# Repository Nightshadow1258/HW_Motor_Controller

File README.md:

# Motor Controller Board - Hardware
Hardware design files and documentation for the 3-phase custom Motor Controller Board (Hardware Revision v1.0). This board is designed for precise BLDC motor control, featuring integrated current sensing, reverse polarity protection, dynamic gate driving, and onboard networking interfaces.
## Board Status
- Current Hardware Version: v1.0
- Status: Tested & Verified (Timer PWM generation, ADC sampling, and hardware bringup verified)
## Key Hardware Components
- MCU: STM32H750VB — High-performance ARM Cortex-M7 Microcontroller (16-bit ADCs, TIM1 Advanced Timer)
- Gate Driver Unit (GDU): DRV8334 — 3-Phase Smart Gate Driver with integrated Current Sense Amplifiers (CSA)
- Ethernet PHY: LAN8742A — 10/100 Ethernet Transceiver for high-speed network communication
- CAN Transceiver: TJA1043T — High-speed CAN Transceiver with sleep mode and wake-up capabilities
- Reverse Polarity Protection (RPP): LM74700 — Ideal Diode Controller for low-loss battery/power reverse polarity protection
- Thermal Sensor: NTCS0603E3103FLT — 10kΩ NTC Thermistor for board temperature monitoring
## Repository Contents
- `/KiCAD` - source schematics files
- `/Documentation/Schematics` — schematic PDF export

# Related Resources
- Firmware Repository: [Motor Controller Board Firmware](https://github.com/Nightshadow1258/FW_STM32H750VB_DRV8334)
- Blog Posts:
	- [Part I - Hardware Design & Bringup](https://blog.preisch.cloud/diy-motor-controller-part-i-hardware-design-bringup/)

# License
This hardware design is licensed under the CERN-OHL-P v2

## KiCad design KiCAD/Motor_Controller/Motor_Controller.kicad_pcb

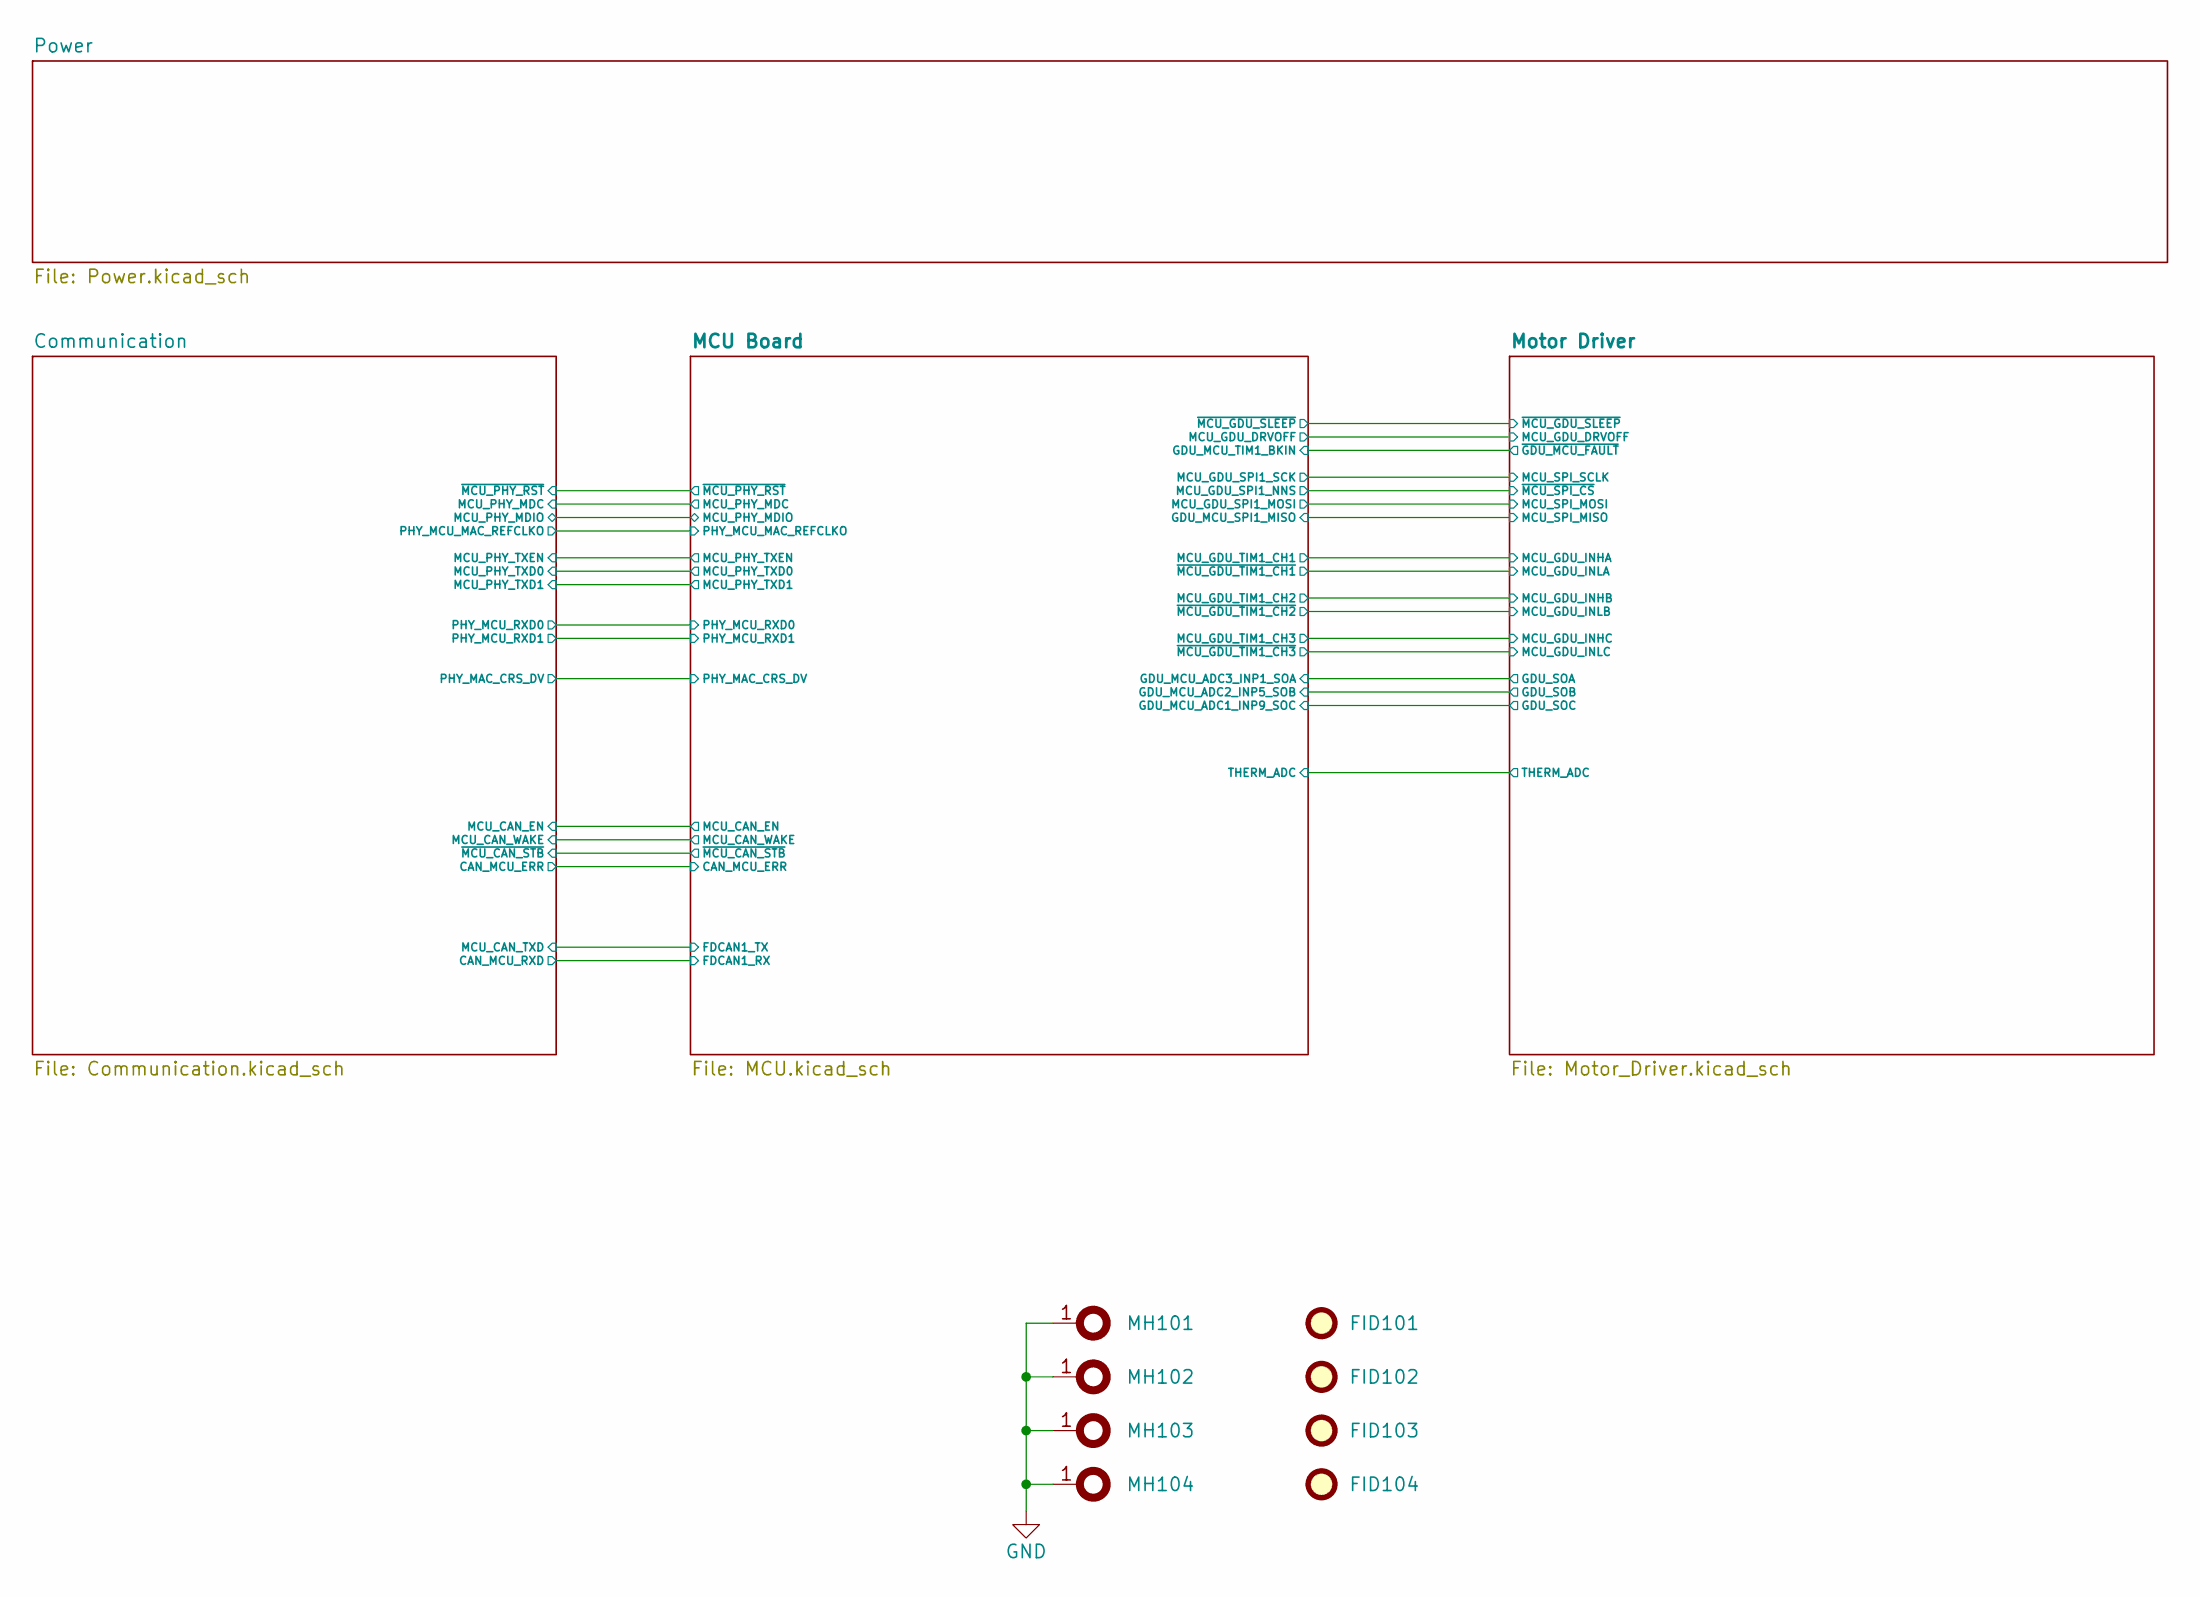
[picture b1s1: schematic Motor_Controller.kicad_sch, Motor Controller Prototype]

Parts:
FID101, FID102, FID103, FID104: Fiducal-JLCPPCB; PCB-FID-JLCPCB
MH101, MH102, MH103, MH104: MountingHole_3.2mm_M3_Pad_Via

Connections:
GND: MH101.1, MH102.1, MH103.1, MH104.1; also elsewhere on the board

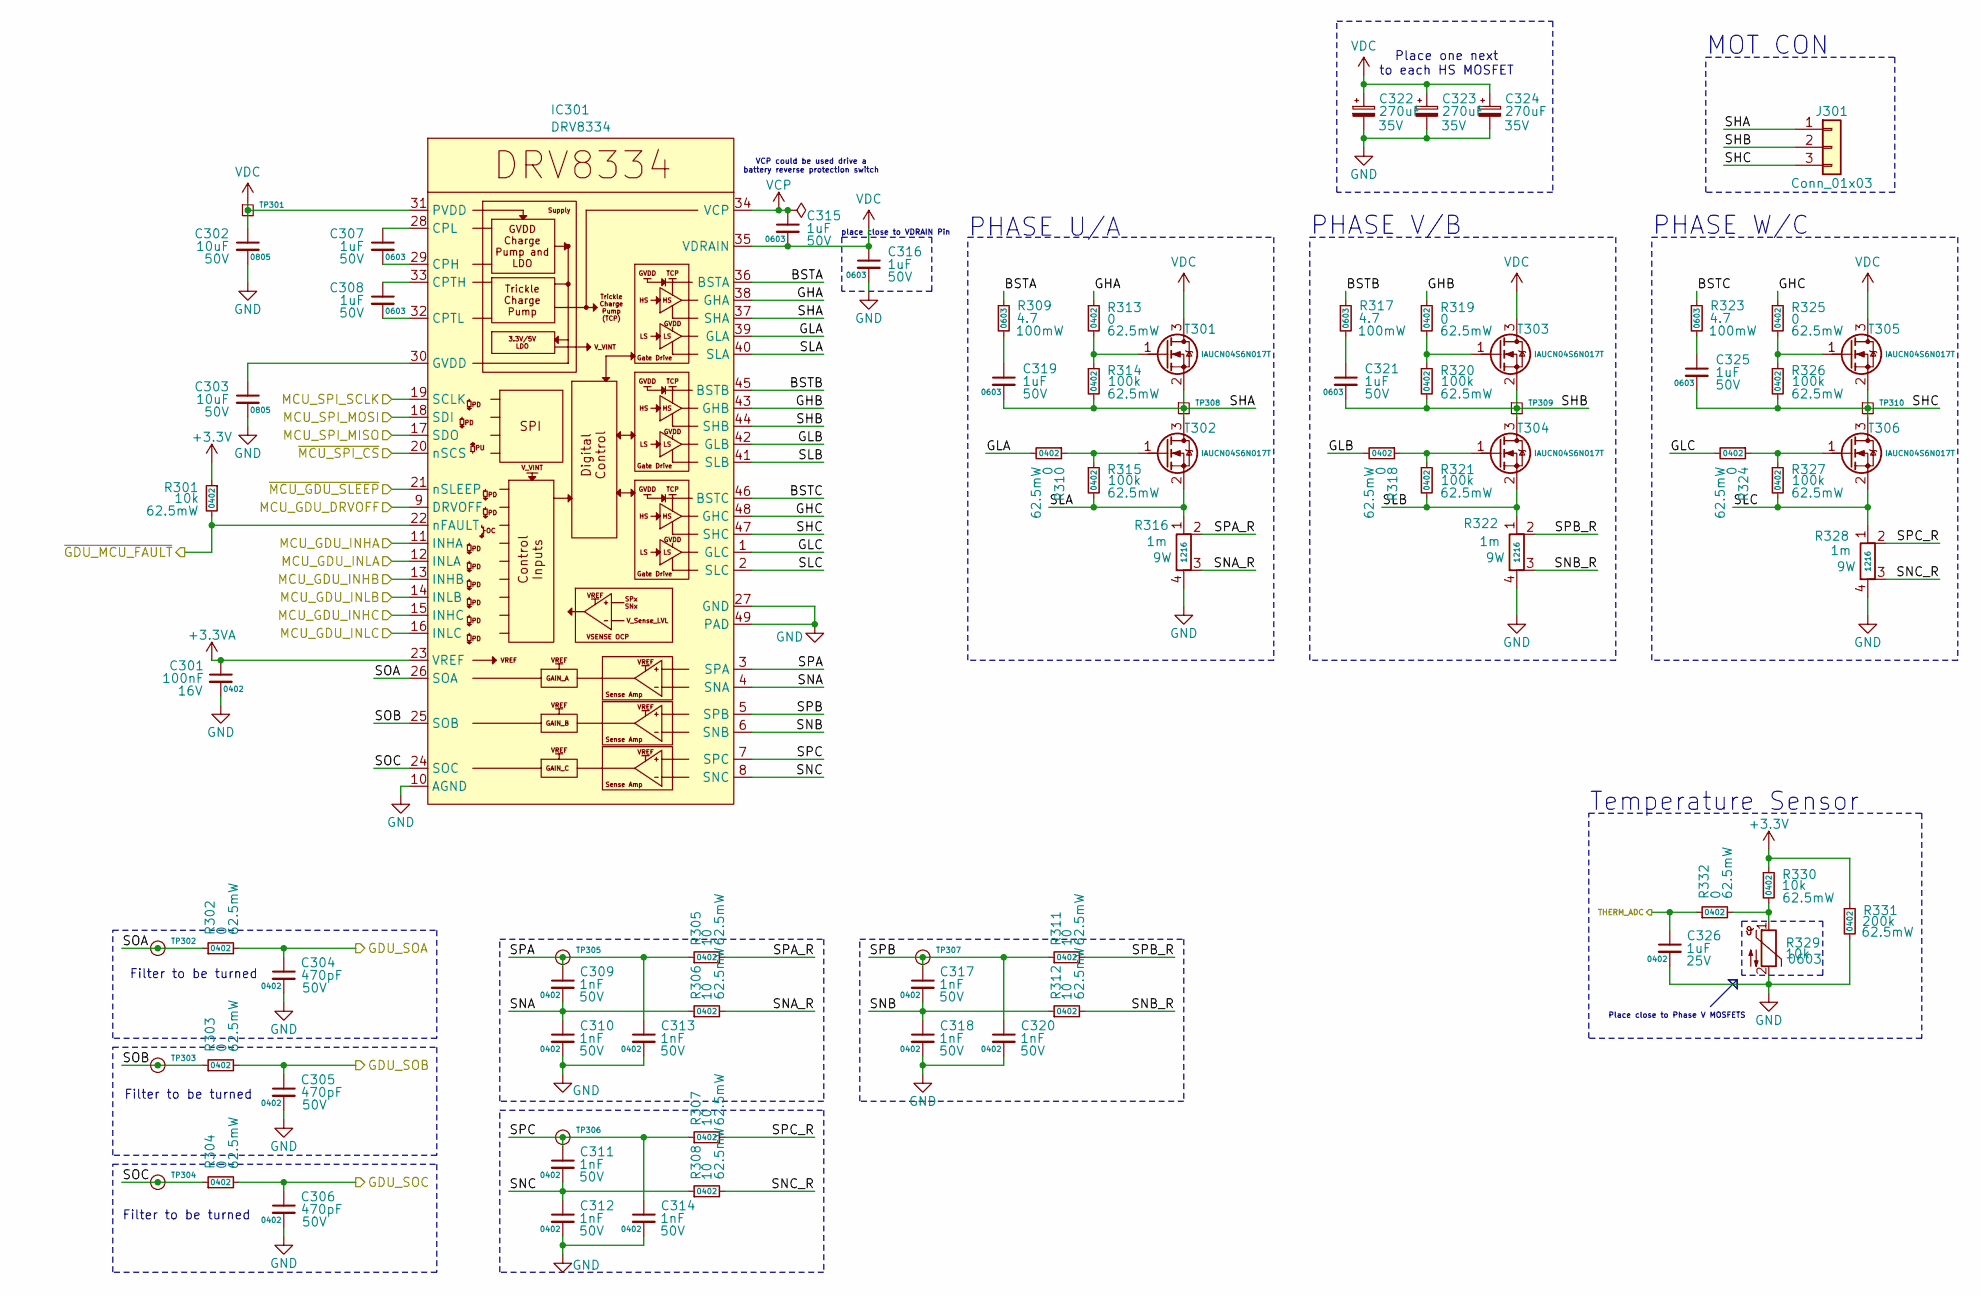
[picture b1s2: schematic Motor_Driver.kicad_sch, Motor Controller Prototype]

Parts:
C301: 100nF; C_0402_1005Metric; Voltage 16V; LCSC Part # C1525
C302, C303: 10uF; C_0805_2012Metric; Voltage 50V; LCSC Part # C440198
C304, C305, C306: 470pF; C_0402_1005Metric; Voltage 50V; LCSC Part # C1537
C307, C308, C315, C316, C319, C321, C325: 1uF; C_0603_1608Metric; Voltage 50V; LCSC Part # C15849
C309, C310, C311, C312, C313, C314, C317, C318, C320: 1nF; C_0402_1005Metric; Voltage 50V; LCSC Part # C1523
C322, C323, C324: 270uF; CP_Elec_10x10; LCSC Part # C79124
C326: 1uF; C_0402_1005Metric; Voltage 25V; LCSC Part # C52923
IC301: DRV8334; Texas_PHP0048E_HTQFP-48-1EP_7x7mm_P0.5mm_EP6.5x6.5mm_Mask3.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; LCSC Part # C32712900
J301: Conn_01x03; CON-01x03-10-AWG
R301, R330: 10k; R_0402_1005Metric; Power Rating 62.5mW; LCSC Part # C25744
R302, R303, R304, R310, R313, R318, R319, R324, R325, R332: 0; R_0402_1005Metric; Power Rating 62.5mW; LCSC Part # C17168
R305, R306, R307, R308, R311, R312: 10; R_0402_1005Metric; Power Rating 62.5mW; LCSC Part # C25077
R309, R317, R323: 4.7; R_0603_1608Metric; Power Rating 100mW; LCSC Part # C23164
R314, R315, R320, R321, R326, R327: 100k; R_0402_1005Metric; Power Rating 62.5mW; LCSC Part # C25741
R316, R322, R328: 1m; R-SH-1216_flip; Power Rating 9W
R329: 10k; R_0603_1608Metric; LCSC Part # C142556
R331: 200k; R_0402_1005Metric; Power Rating 62.5mW; LCSC Part # C25764
T301, T302, T303, T304, T305, T306: IAUCN04S6N017T; T-MOSN-LHDSO-10-1
TP301, TP308, TP309, TP310: Testpoint-BASE; TP_THT_D0.8mm
TP302, TP303, TP304, TP305, TP306, TP307: TP; TP_Pad_D0.9mm

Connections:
+3.3V: R301.1, R330.1, R331.1; also elsewhere on the board
+3.3VA: C301.1, IC301.23 (VREF); also elsewhere on the board
/MCU Board/GDU_MCU_ADC1_INP9_SOA: C304.1, R302.2; also elsewhere on the board
/MCU Board/GDU_MCU_ADC2_INP5_SOB: C305.1, R303.2; also elsewhere on the board
/MCU Board/GDU_MCU_ADC3_INP1_SOC: C306.1, R304.2; also elsewhere on the board
/MCU Board/GDU_MCU_SPI1_MISO: IC301.17 (SDO); also elsewhere on the board
/MCU Board/GDU_MCU_TIM1_BKIN: IC301.22 (nFAULT), R301.2; also elsewhere on the board
/MCU Board/MCU_GDU_DRVOFF: IC301.9 (DRVOFF); also elsewhere on the board
/MCU Board/MCU_GDU_SPI1_MOSI: IC301.18 (SDI); also elsewhere on the board
/MCU Board/MCU_GDU_SPI1_NNS: IC301.20 (nSCS); also elsewhere on the board
/MCU Board/MCU_GDU_SPI1_SCK: IC301.19 (SCLK); also elsewhere on the board
/MCU Board/MCU_GDU_TIM1_CH1: IC301.11 (INHA); also elsewhere on the board
/MCU Board/MCU_GDU_TIM1_CH2: IC301.13 (INHB); also elsewhere on the board
/MCU Board/MCU_GDU_TIM1_CH3: IC301.15 (INHC); also elsewhere on the board
/MCU Board/THERM_ADC: C326.1, R332.1; also elsewhere on the board
/MCU Board/~MCU_GDU_SLEEP: IC301.21 (nSLEEP); also elsewhere on the board
/MCU Board/~MCU_GDU_TIM1_CH1: IC301.12 (INLA); also elsewhere on the board
/MCU Board/~MCU_GDU_TIM1_CH2: IC301.14 (INLB); also elsewhere on the board
/MCU Board/~MCU_GDU_TIM1_CH3: IC301.16 (INLC); also elsewhere on the board
/Motor Driver/BSTA: IC301.36 (BSTA), R309.1
/Motor Driver/BSTB: IC301.45 (BSTB), R317.1
/Motor Driver/BSTC: IC301.46 (BSTC), R323.1
/Motor Driver/GHA: IC301.38 (GHA), R313.1
/Motor Driver/GHB: IC301.43 (GHB), R319.1
/Motor Driver/GHC: IC301.48 (GHC), R325.1
/Motor Driver/GLA: IC301.39 (GLA), R310.2
/Motor Driver/GLB: IC301.42 (GLB), R318.2
/Motor Driver/GLC: IC301.1 (GLC), R324.2
/Motor Driver/SHA: C319.2, IC301.37 (SHA), J301.1, R314.2, T301.2 (S), T302.3 (D), TP308.1
/Motor Driver/SHB: C321.2, IC301.44 (SHB), J301.2, R320.2, T303.2 (S), T304.3 (D), TP309.1
/Motor Driver/SHC: C325.2, IC301.47 (SHC), J301.3, R326.2, T305.2 (S), T306.3 (D), TP310.1
/Motor Driver/SLA: IC301.40 (SLA), R315.2, R316.1, T302.2 (S)
/Motor Driver/SLB: IC301.41 (SLB), R321.2, R322.1, T304.2 (S)
/Motor Driver/SLC: IC301.2 (SLC), R327.2, R328.1, T306.2 (S)
/Motor Driver/SNA: C309.2, C310.1, IC301.4 (SNA), R306.1
/Motor Driver/SNA_R: R306.2, R316.3
/Motor Driver/SNB: C317.2, C318.1, IC301.6 (SNB), R312.1
/Motor Driver/SNB_R: R312.2, R322.3
/Motor Driver/SNC: C311.2, C312.1, IC301.8 (SNC), R308.1
/Motor Driver/SNC_R: R308.2, R328.3
/Motor Driver/SOA: IC301.26 (SOA), R302.1, TP302.1
/Motor Driver/SOB: IC301.25 (SOB), R303.1, TP303.1
/Motor Driver/SOC: IC301.24 (SOC), R304.1, TP304.1
/Motor Driver/SPA: C309.1, C313.1, IC301.3 (SPA), R305.1, TP305.1
/Motor Driver/SPA_R: R305.2, R316.2
/Motor Driver/SPB: C317.1, C320.1, IC301.5 (SPB), R311.1, TP307.1
/Motor Driver/SPB_R: R311.2, R322.2
/Motor Driver/SPC: C311.1, C314.1, IC301.7 (SPC), R307.1, TP306.1
/Motor Driver/SPC_R: R307.2, R328.2
GND: C301.2, C302.2, C303.2, C304.2, C305.2, C306.2, C310.2, C312.2, C313.2, C314.2, C316.2, C318.2, C320.2, C322.2, C323.2, C324.2, C326.2, IC301.10 (AGND), IC301.27 (GND), IC301.49 (PAD), R316.4, R322.4, R328.4, R329.2, R331.2; also elsewhere on the board
unnamed: C319.1, R309.2
unnamed: C321.1, R317.2
unnamed: C325.1, R323.2
unnamed: C307.2, IC301.29 (CPH)
unnamed: C307.1, IC301.28 (CPL)
unnamed: C308.1, IC301.33 (CPTH)
unnamed: C308.2, IC301.32 (CPTL)
unnamed: C303.1, IC301.30 (GVDD)
unnamed: R329.1, R330.2, R332.2
unnamed: R313.2, R314.1, T301.1 (G)
unnamed: R310.1, R315.1, T302.1 (G)
unnamed: R319.2, R320.1, T303.1 (G)
unnamed: R318.1, R321.1, T304.1 (G)
unnamed: R325.2, R326.1, T305.1 (G)
unnamed: R324.1, R327.1, T306.1 (G)
VCP: C315.1, IC301.34 (VCP)
VDC: C302.1, C315.2, C316.1, C322.1, C323.1, C324.1, IC301.31 (PVDD), IC301.35 (VDRAIN), T301.3 (D), T303.3 (D), T305.3 (D), TP301.1; also elsewhere on the board

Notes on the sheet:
PHASE U/A
place close to VDRAIN Pin
Place close to Phase V MOSFETS
Filter to be turned
PHASE V/B
Place one next to each HS MOSFET
MOT CON
PHASE W/C
Temperature Sensor
VCP could be used drive a battery reverse protection switch

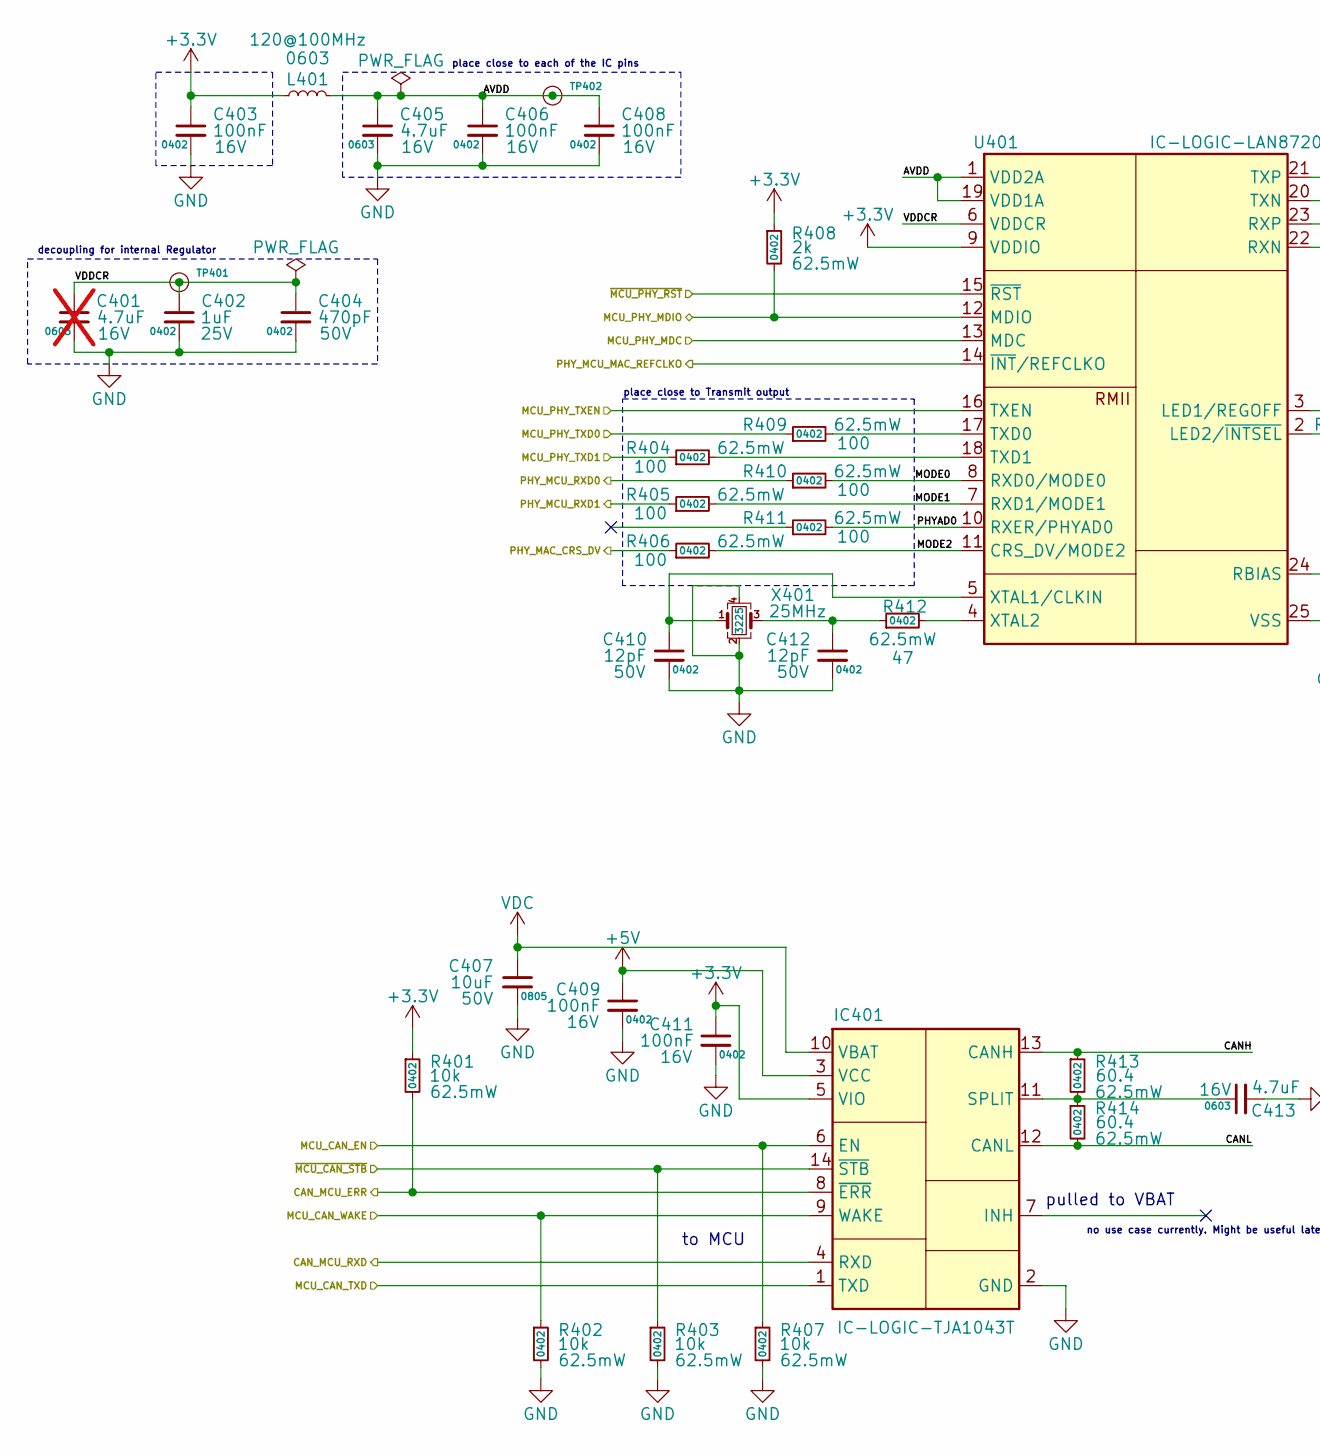
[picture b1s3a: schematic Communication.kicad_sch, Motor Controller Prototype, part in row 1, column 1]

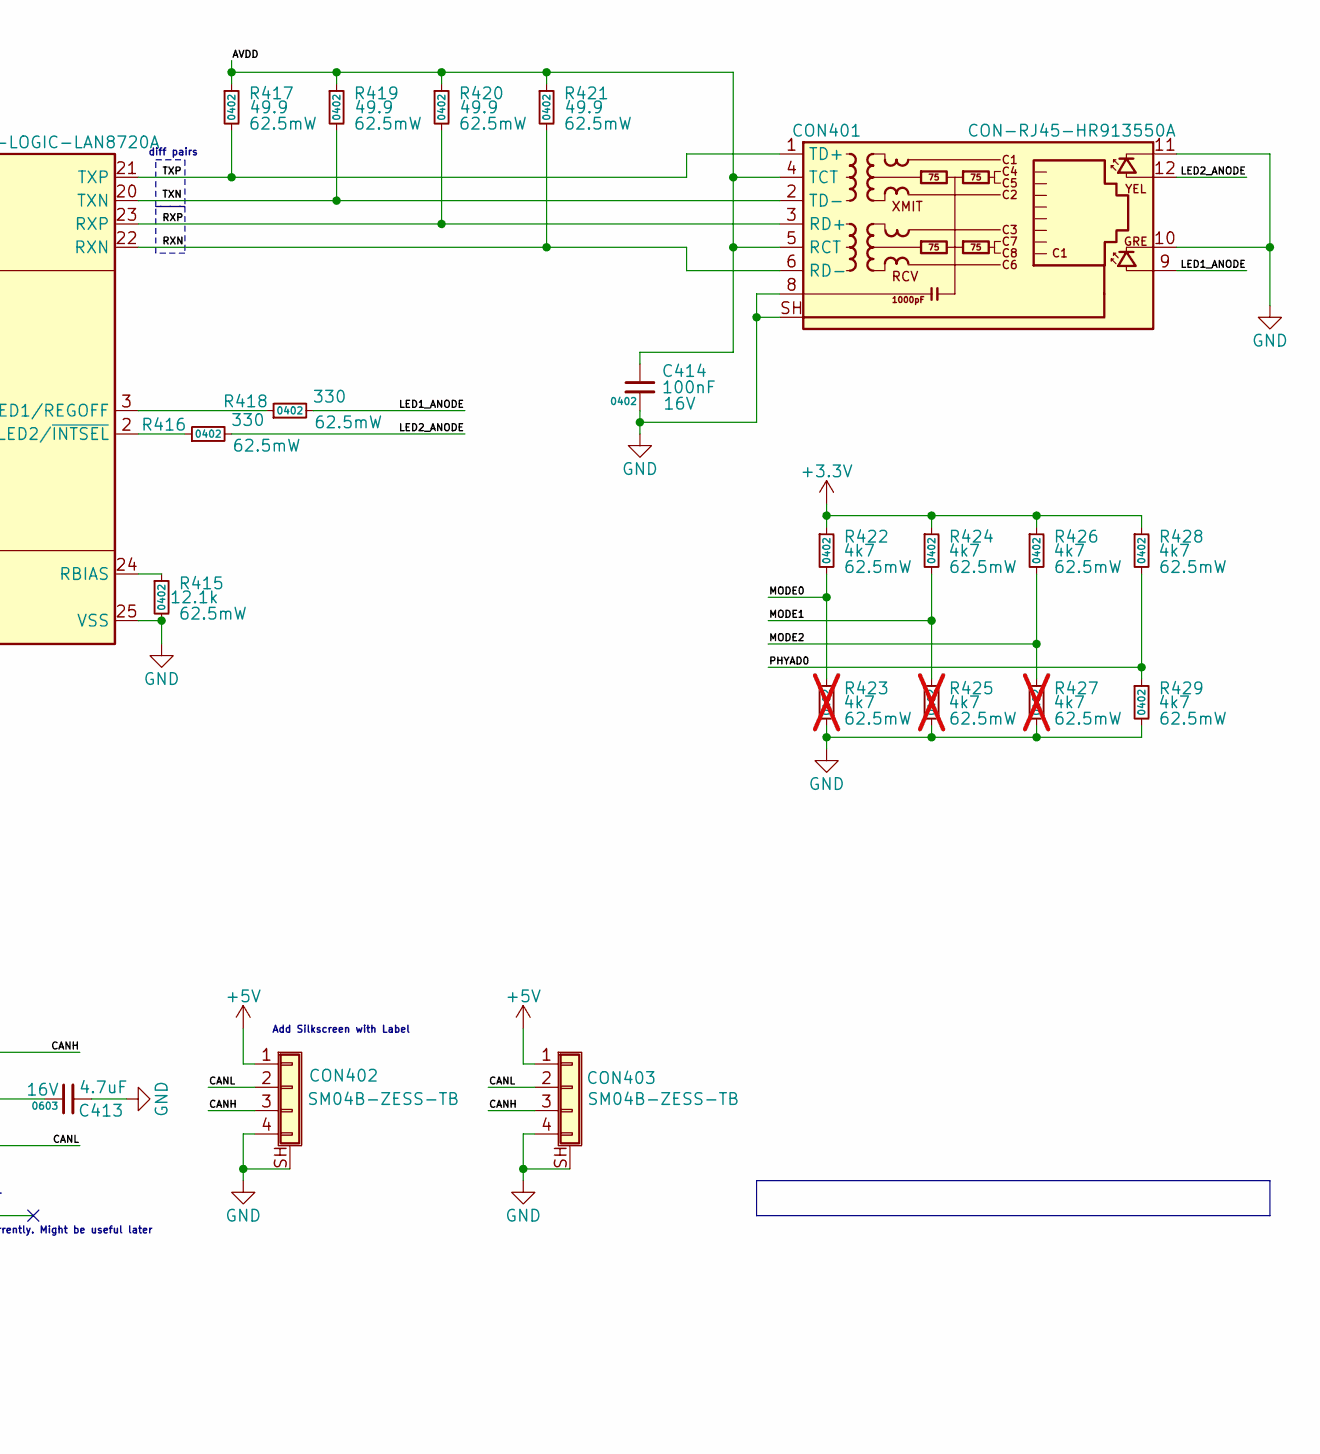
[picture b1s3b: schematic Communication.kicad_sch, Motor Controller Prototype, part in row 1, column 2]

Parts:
C401: 4.7uF; C_0603_1608Metric; Voltage 16V; LCSC Part # C19666; not fitted
C402: 1uF; C_0402_1005Metric; Voltage 25V; LCSC Part # C52923
C403, C406, C408, C409, C411, C414: 100nF; C_0402_1005Metric; Voltage 16V; LCSC Part # C1525
C404: 470pF; C_0402_1005Metric; Voltage 50V; LCSC Part # C1537
C405, C413: 4.7uF; C_0603_1608Metric; Voltage 16V; LCSC Part # C19666
C407: 10uF; C_0805_2012Metric; Voltage 50V; LCSC Part # C440198
C410, C412: 12pF; C_0402_1005Metric; Voltage 50V; LCSC Part # C1547
CON401: CON-RJ45-HR913550A; CON-RJ45-HR911105A-H; LCSC Part # C163507
CON402, CON403: SM04B-ZESS-TB; CON-SM04B-ZESS-TB
IC401: IC-LOGIC-TJA1043T; SOIC-14_3.9x8.7mm_P1.27mm; LCSC Part # C140826
L401: FB-BLM18PG121SN1; L_0603_1608Metric; LCSC Part # C14709
R401, R402, R403, R407: 10k; R_0402_1005Metric; Power Rating 62.5mW; LCSC Part # C25744
R404, R405, R406, R409, R410, R411: 100; R_0402_1005Metric; Power Rating 62.5mW; LCSC Part # C25076
R408: 2k; R_0402_1005Metric; Power Rating 62.5mW; LCSC Part # C4109
R412: 47; R_0402_1005Metric; Power Rating 62.5mW; LCSC Part # C25118
R413, R414: 60.4; R_0402_1005Metric; Power Rating 62.5mW; LCSC Part # C60310
R415: 12.1k; R_0402_1005Metric; Power Rating 62.5mW; LCSC Part # C25852
R416, R418: 330; R_0402_1005Metric; Power Rating 62.5mW; LCSC Part # C25104
R417, R419, R420, R421: 49.9; R_0402_1005Metric; Power Rating 62.5mW; LCSC Part # C25120
R422, R424, R426, R428, R429: 4k7; R_0402_1005Metric; Power Rating 62.5mW; LCSC Part # C25900
R423, R425, R427: 4k7; R_0402_1005Metric; Power Rating 62.5mW; LCSC Part # C25900; not fitted
TP401, TP402: TP; TP_Pad_D0.9mm
U401: IC-LOGIC-LAN8720A; VQFN-24-1EP_4x4mm_P0.5mm_EP2.5x2.5mm_ThermalVias; LCSC Part # C621425
X401: 25MHz; Crystal_SMD_3225-4Pin_3.2x2.5mm; LCSC Part # C9006

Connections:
+3.3V: C403.1, C411.1, IC401.5 (VIO), L401.1, R401.1, R408.1, R422.1, R424.1, R426.1, R428.1, U401.9 (VDDIO); also elsewhere on the board
+5V: C409.1, CON402.1, CON403.1, IC401.3 (VCC); also elsewhere on the board
/Communication/AVDD: C405.1, C406.1, C408.1, C414.1, CON401.4 (TCT), CON401.5 (RCT), L401.2, R417.1, R419.1, R420.1, R421.1, TP402.1, U401.1 (VDD2A), U401.19 (VDD1A)
/Communication/CANH: CON402.3, CON403.3, IC401.13 (CANH), R413.1
/Communication/CANL: CON402.2, CON403.2, IC401.12 (CANL), R414.2
/Communication/CAN_MCU_ERR: IC401.8 (~ERR), R401.2; also elsewhere on the board
/Communication/CAN_MCU_RXD: IC401.4 (RXD); also elsewhere on the board
/Communication/LED1_ANODE: CON401.9, R418.2
/Communication/LED2_ANODE: CON401.12, R416.2
/Communication/MCU_CAN_EN: IC401.6 (EN), R407.1; also elsewhere on the board
/Communication/MCU_CAN_TXD: IC401.1 (TXD); also elsewhere on the board
/Communication/MCU_CAN_WAKE: IC401.9 (WAKE), R402.1; also elsewhere on the board
/Communication/MCU_PHY_MDC: U401.13 (MDC); also elsewhere on the board
/Communication/MCU_PHY_MDIO: R408.2, U401.12 (MDIO); also elsewhere on the board
/Communication/MCU_PHY_TXD0: R409.1; also elsewhere on the board
/Communication/MCU_PHY_TXD1: R404.1; also elsewhere on the board
/Communication/MCU_PHY_TXEN: U401.16 (TXEN); also elsewhere on the board
/Communication/MODE0: R410.2, R422.2, R423.1, U401.8 (RXD0/MODE0)
/Communication/MODE1: R405.2, R424.2, R425.1, U401.7 (RXD1/MODE1)
/Communication/MODE2: R406.2, R426.2, R427.1, U401.11 (CRS_DV/MODE2)
/Communication/PHYAD0: R411.2, R428.2, R429.1, U401.10 (RXER/PHYAD0)
/Communication/PHY_MAC_CRS_DV: R406.1; also elsewhere on the board
/Communication/PHY_MCU_MAC_REFCLKO: U401.14 (~INT/REFCLKO); also elsewhere on the board
/Communication/PHY_MCU_RXD0: R410.1; also elsewhere on the board
/Communication/PHY_MCU_RXD1: R405.1; also elsewhere on the board
/Communication/RXN: CON401.6 (RD-), R421.2, U401.22 (RXN)
/Communication/RXP: CON401.3 (RD+), R420.2, U401.23 (RXP)
/Communication/TXN: CON401.2 (TD-), R419.2, U401.20 (TXN)
/Communication/TXP: CON401.1 (TD+), R417.2, U401.21 (TXP)
/Communication/VDDCR: C401.1, C402.1, C404.1, TP401.1, U401.6 (VDDCR)
/Communication/~MCU_CAN_STB: IC401.14 (~STB), R403.1; also elsewhere on the board
/Communication/~MCU_PHY_RST: U401.15 (~RST); also elsewhere on the board
GND: C401.2, C402.2, C403.2, C404.2, C405.2, C406.2, C407.2, C408.2, C409.2, C410.2, C411.2, C412.2, C413.2, C414.2, CON401.8, CON401.10, CON401.11, CON401.SH, CON402.4, CON402.SH (Shield), CON403.4, CON403.SH (Shield), IC401.2 (GND), R402.2, R403.2, R407.2, R415.2, R423.2, R425.2, R427.2, R429.2, U401.25 (VSS), X401.2, X401.4; also elsewhere on the board
unnamed: C412.1, R412.1, X401.3
unnamed: C413.1, IC401.11 (SPLIT), R413.2, R414.1
unnamed: R418.1, U401.3 (LED1/REGOFF)
unnamed: R416.1, U401.2 (LED2/~INTSEL)
unnamed: R415.1, U401.24 (RBIAS)
unnamed: R409.2, U401.17 (TXD0)
unnamed: R404.2, U401.18 (TXD1)
unnamed: C410.1, U401.5 (XTAL1/CLKIN), X401.1
unnamed: R412.2, U401.4 (XTAL2)
VDC: C407.1, IC401.10 (VBAT); also elsewhere on the board

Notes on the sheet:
pulled to VBAT
place close to Transmit output
place close to each of the IC pins
to MCU
Add Silkscreen with Label
diff pairs
decoupling for internal Regulator
no use case currently. Might be useful later
